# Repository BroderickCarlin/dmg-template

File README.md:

# dmg-template
Template project for using a DMG Gameboy as a project enclosure

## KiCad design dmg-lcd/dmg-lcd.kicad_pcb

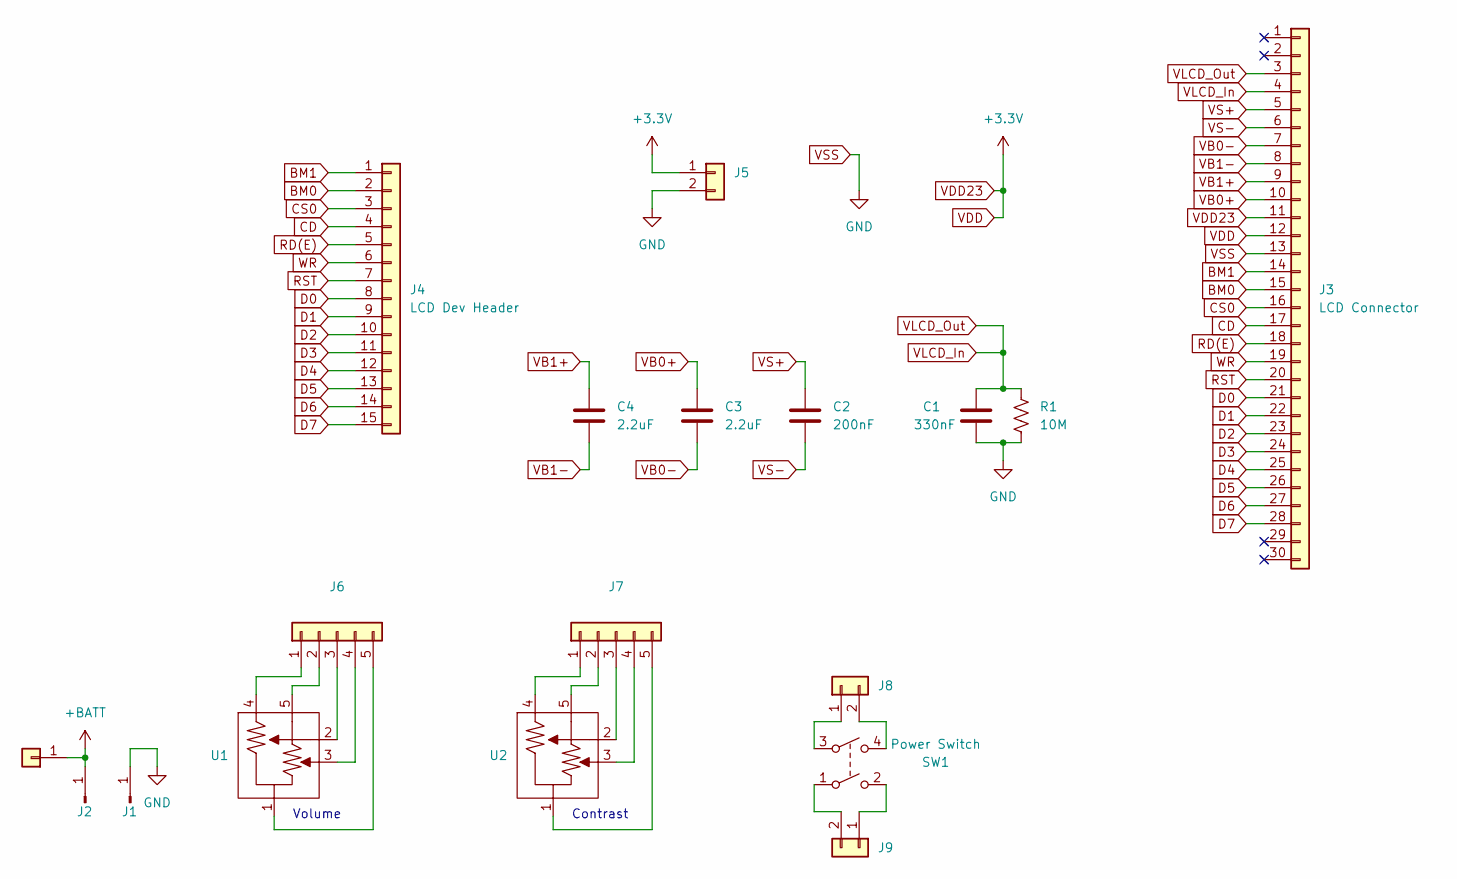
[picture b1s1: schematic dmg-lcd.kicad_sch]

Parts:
C1: 330nF; C_0603_1608Metric
C2: 200nF; C_1206_3216Metric
C3, C4: 2.2uF; C_0603_1608Metric
J1, J2: Conn_01x01_Pin; Battery_Terminal
J3: LCD Connector; TE_3-1734839-0_1x30-1MP_P0.5mm_Horizontal
J4: LCD Dev Header; PinHeader_1x15_P2.54mm_Vertical
J5, J8, J9: Conn_01x02; PinHeader_1x02_P2.54mm_Vertical
J6, J7: Conn_01x05; PinHeader_1x05_P2.54mm_Vertical
J10: Conn_01x01; PinHeader_1x01_P2.54mm_Vertical
R1: 10M; R_0603_1608Metric
SW1: Power Switch; Power_Switch
U1: Volume_Potentiometer
U2: Contrast_Potentiometer

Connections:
+BATT: J2.1, J10.1
BM0: J3.15, J4.2
BM1: J3.14, J4.1
CD: J3.17, J4.4
CS0: J3.16, J4.3
D0: J3.21, J4.8
D1: J3.22, J4.9
D2: J3.23, J4.10
D3: J3.24, J4.11
D4: J3.25, J4.12
D5: J3.26, J4.13
D6: J3.27, J4.14
D7: J3.28, J4.15
unnamed: J6.1, U1.4
unnamed: J6.2, U1.5
unnamed: J6.3, U1.2
unnamed: J6.4, U1.3
unnamed: J6.5, U1.1
unnamed: J7.1, U2.4
unnamed: J7.2, U2.5
unnamed: J7.3, U2.2
unnamed: J7.4, U2.3
unnamed: J7.5, U2.1
unnamed: J8.1, SW1.3
unnamed: J8.2, SW1.4
unnamed: J9.1, SW1.2
unnamed: J9.2, SW1.1
RD(E): J3.18, J4.5
RST: J3.20, J4.7
VB0+: C3.1, J3.10
VB0-: C3.2, J3.7
VB1+: C4.1, J3.9
VB1-: C4.2, J3.8
VDD: J3.11, J3.12, J5.1
VLCD_In: C1.1, J3.3, J3.4, R1.1
VS+: C2.1, J3.5
VS-: C2.2, J3.6
VSS: C1.2, J1.1, J3.13, J5.2, R1.2
WR: J3.19, J4.6

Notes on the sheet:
Contrast
Volume

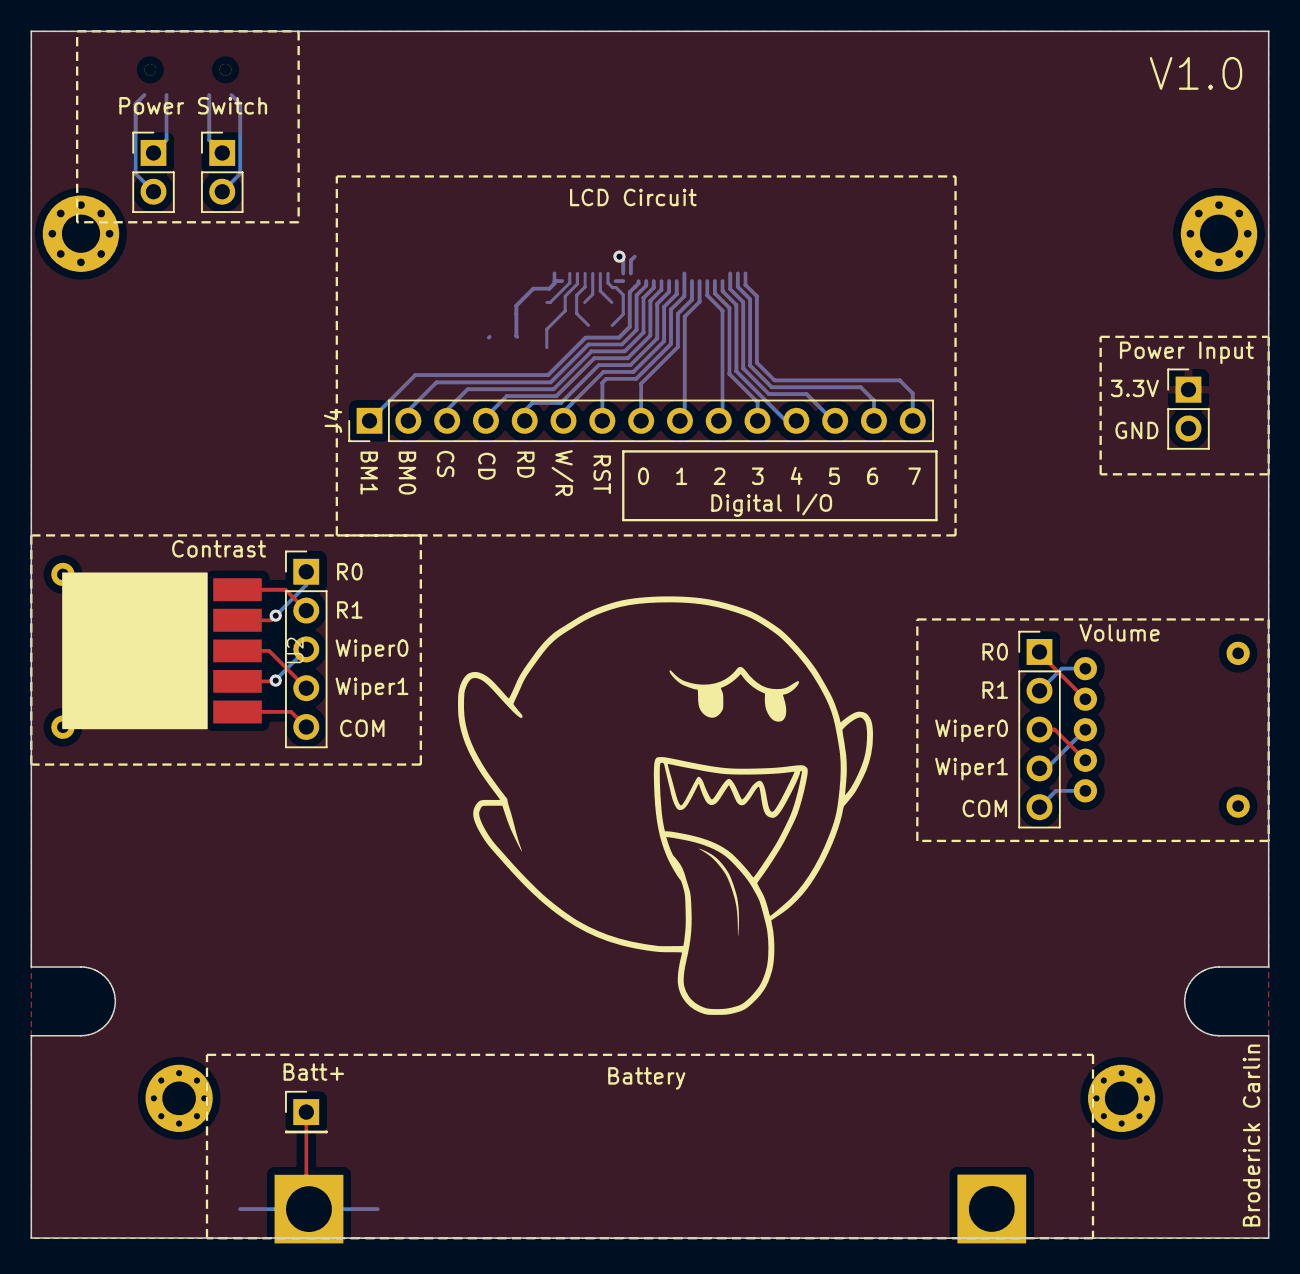
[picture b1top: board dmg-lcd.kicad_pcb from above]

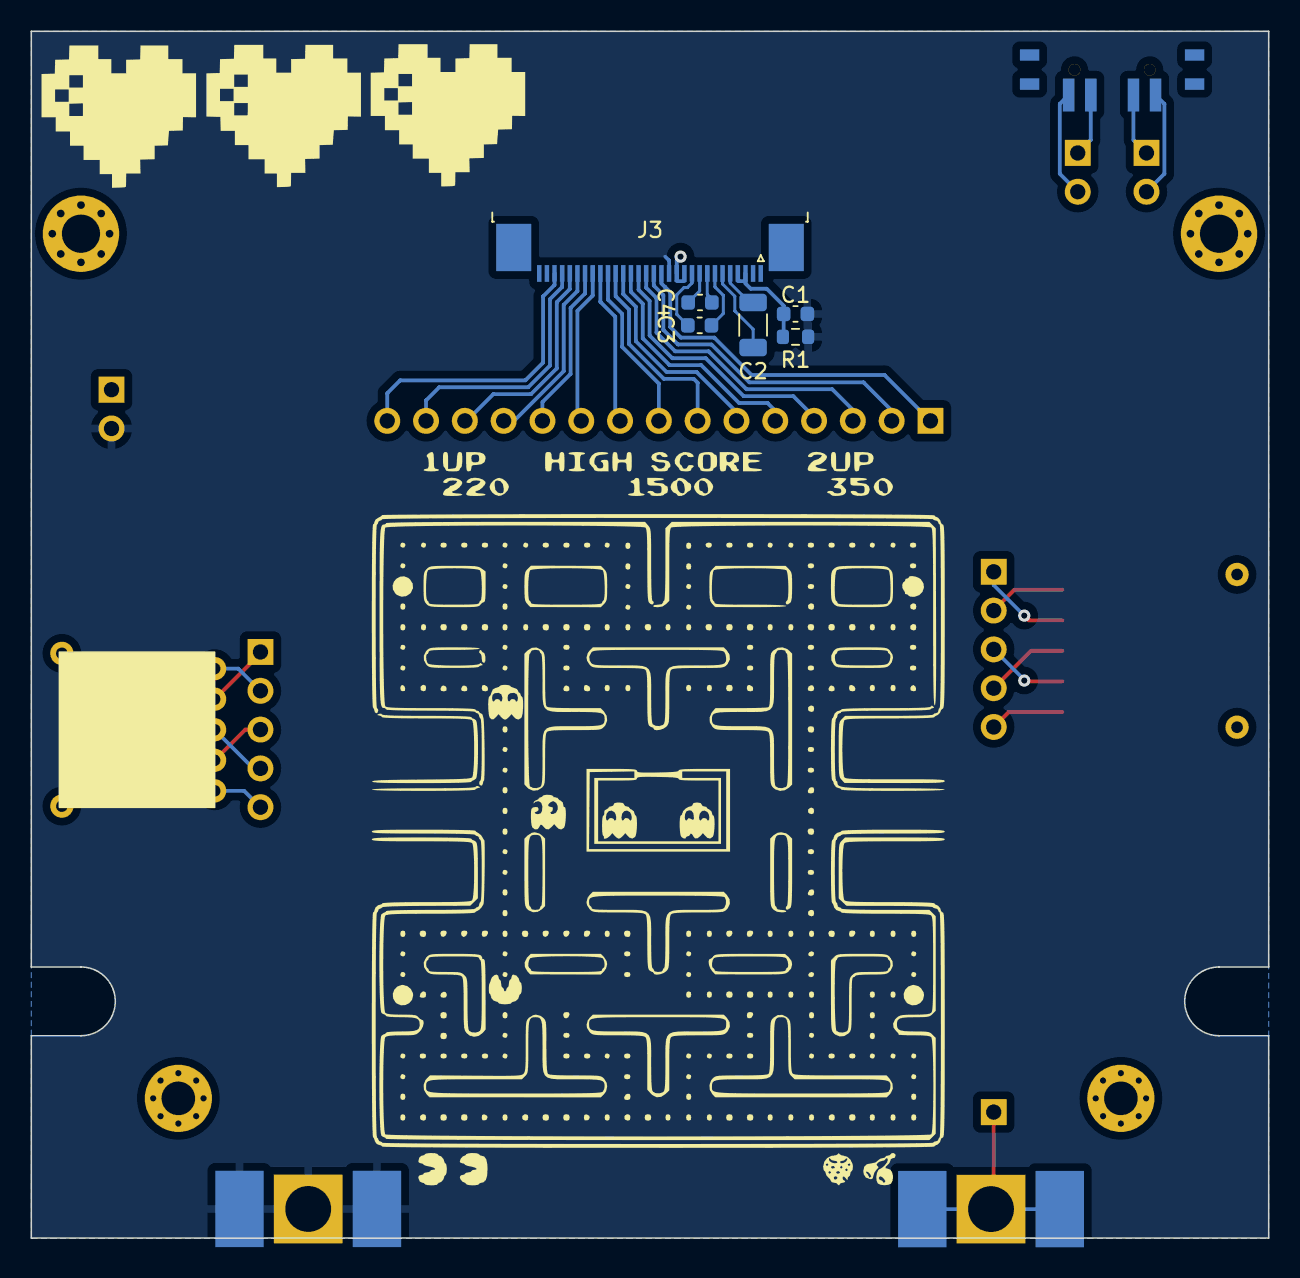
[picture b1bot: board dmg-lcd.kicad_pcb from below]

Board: 2 copper layers, 81.0 x 79.0 mm, 18 parts (10 on the bottom side), 39 nets.

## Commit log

2023-11-19 feat: Initial commit with board outline for DMG GB
2023-11-20 feat: Add battery terminals
2023-11-22 feat: Add potentiometers and volumn switch
2023-11-23 feat: V1.0 of the board
2023-11-23 chore: Gerber output config tweak
2023-11-23 feat: Update one of the capacitor footprints to match what is in stock, rerouting too
